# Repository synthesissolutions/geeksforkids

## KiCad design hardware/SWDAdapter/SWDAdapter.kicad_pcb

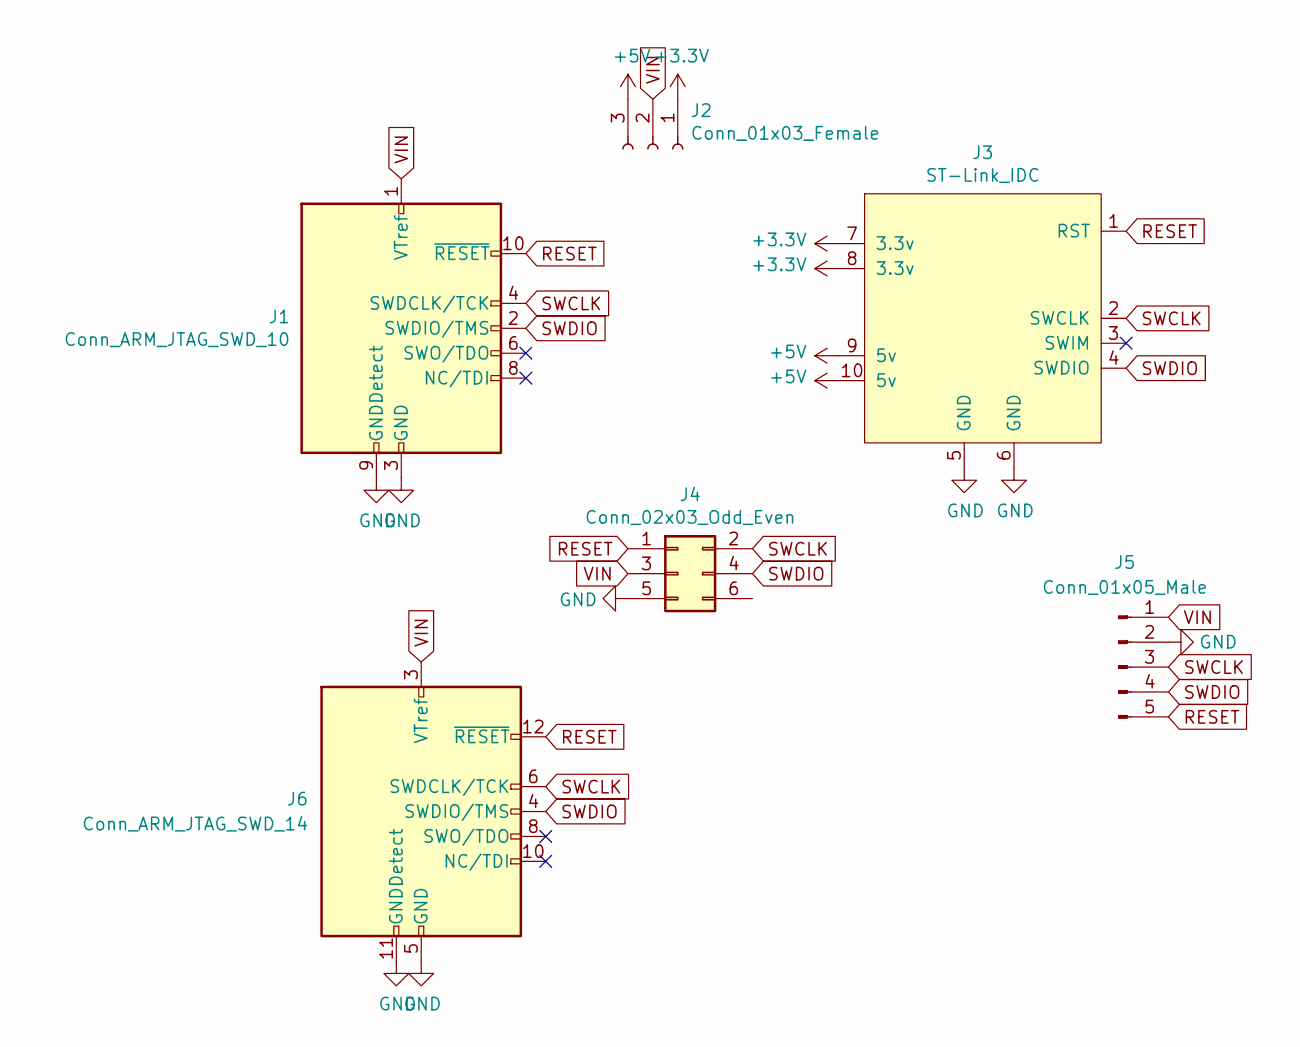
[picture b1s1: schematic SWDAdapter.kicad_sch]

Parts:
J1: Conn_ARM_JTAG_SWD_10; CONN_3220-10-0100-00_CNC
J2: Conn_01x03_Female; PinHeader_1x03_P2.54mm_Vertical
J3: ST-Link_IDC; IDC-Header_2x05_P2.54mm_Vertical
J4: Conn_02x03_Odd_Even; IDC-Header_2x03_P2.54mm_Vertical
J5: Conn_01x05_Male; JST_SH_BM05B-SRSS-TB_1x05-1MP_P1.00mm_Vertical
J6: Conn_ARM_JTAG_SWD_14; SWD14 STLINK-V3-Mini

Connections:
+3V3: J2.1, J3.7 (3.3v), J3.8 (3.3v)
+5V: J2.3, J3.9 (5v), J3.10 (5v)
GND: J1.3 (GND), J1.5 (GND), J1.9 (GNDDetect), J3.5 (GND), J3.6 (GND), J4.5, J5.2, J6.5 (GND), J6.7 (GND), J6.11 (GNDDetect)
RESET: J1.10 (~RESET), J3.1 (RST), J4.1, J5.5, J6.12 (~RESET)
Reserved: J6.1 (Reserved), J6.2 (Reserved), J6.13 (Reserved), J6.14 (Reserved)
SWCLK: J1.4 (SWDCLK/TCK), J3.2 (SWCLK), J4.2, J5.3, J6.6 (SWDCLK/TCK)
SWDIO: J1.2 (SWDIO/TMS), J3.4 (SWDIO), J4.4, J5.4, J6.4 (SWDIO/TMS)
VIN: J1.1 (VTref), J2.2, J4.3, J5.1, J6.3 (VTref)

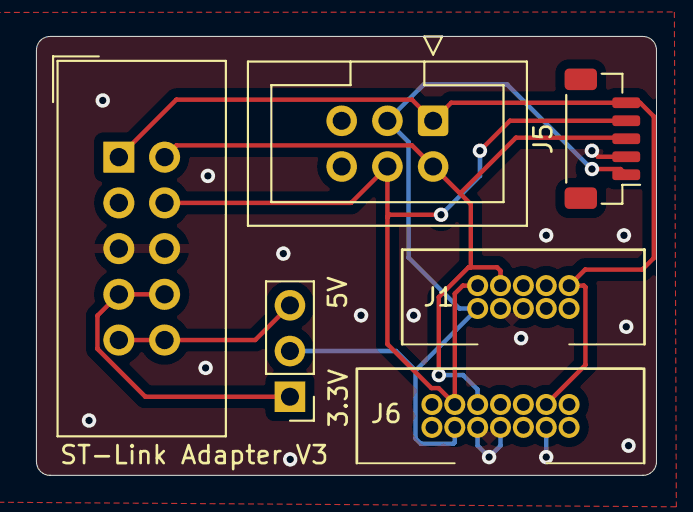
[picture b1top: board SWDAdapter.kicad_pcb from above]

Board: 2 copper layers, 34.4 x 24.4 mm, 6 parts (0 on the bottom side), 8 nets.

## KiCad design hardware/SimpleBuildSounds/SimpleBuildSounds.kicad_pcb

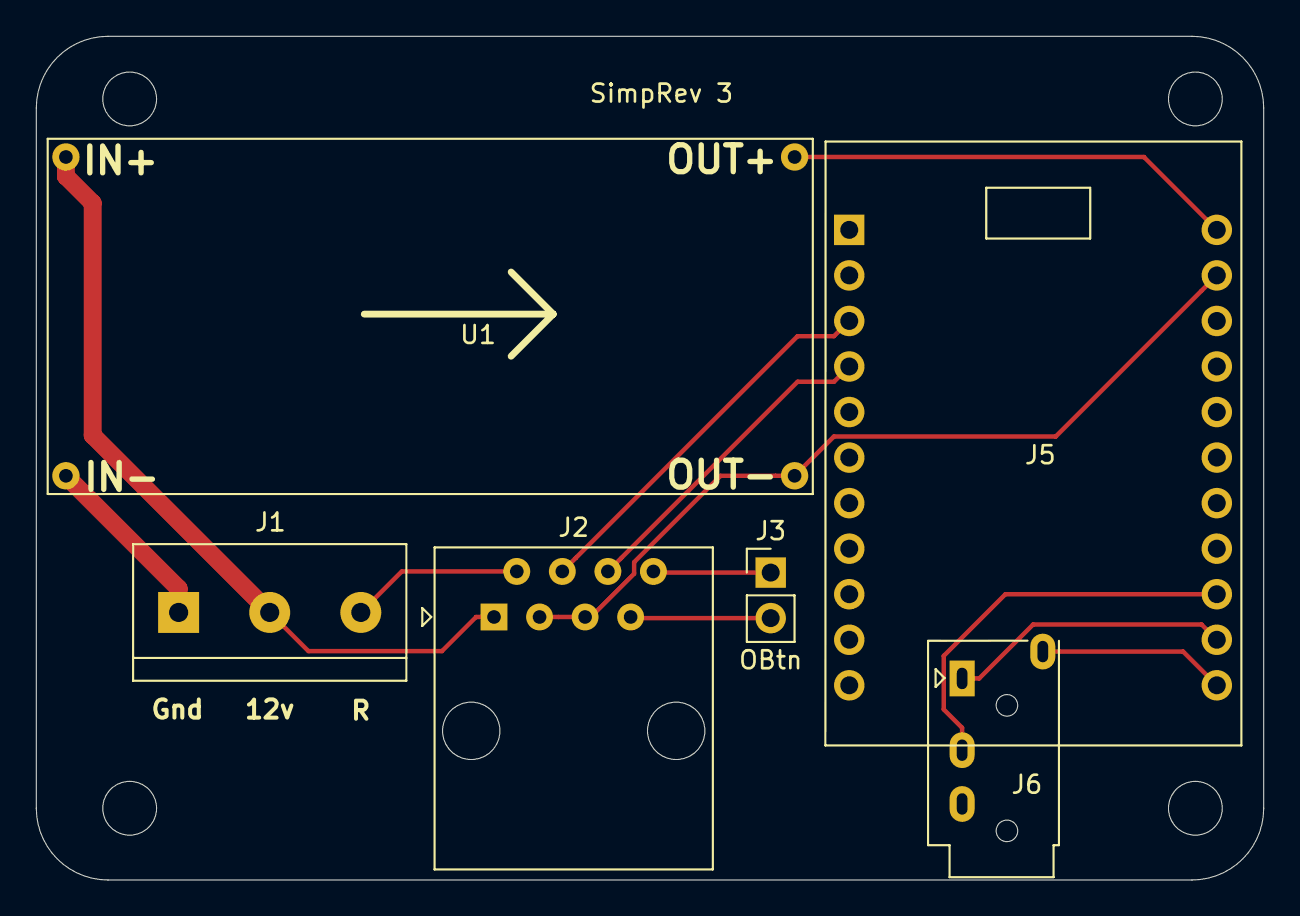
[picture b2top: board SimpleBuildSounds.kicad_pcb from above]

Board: 2 copper layers, 68.5 x 47.1 mm, 10 parts (0 on the bottom side), 12 nets.

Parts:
J1: Power and GoBtn; TerminalBlock_bornier-2_P5.08mm
J2: RJ45; RJ45_Amphenol_54602-x08_Horizontal
J3: OBtn; PinHeader_1x02_P2.54mm_Vertical
J5: FX_Sound; FXSound_2x11_P2.54mm_Short
J6: AudioJack4; Jack_3.5mm_PJ320A_Horizontal
REF: MountingHole_3mm
REF#2, REF#3, REF#4: MountingHole_3mm
U1: LM2596; Regulator_LM2596Adj

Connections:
+5V: J5.2, U1.4
+12V: J1.2, J2.1, U1.2
GND: J2.3, J2.5, J5.4, U1.6
GNDPWR: J1.1, U1.1
unnamed: J1.3, J2.2
unnamed: J2.4, J5.5
unnamed: J2.6, J5.7
unnamed: J2.7, J3.2
unnamed: J2.8, J3.1
unnamed: J5.18, J6.R1
unnamed: J5.20, J6.T
unnamed: J5.22, J6.S

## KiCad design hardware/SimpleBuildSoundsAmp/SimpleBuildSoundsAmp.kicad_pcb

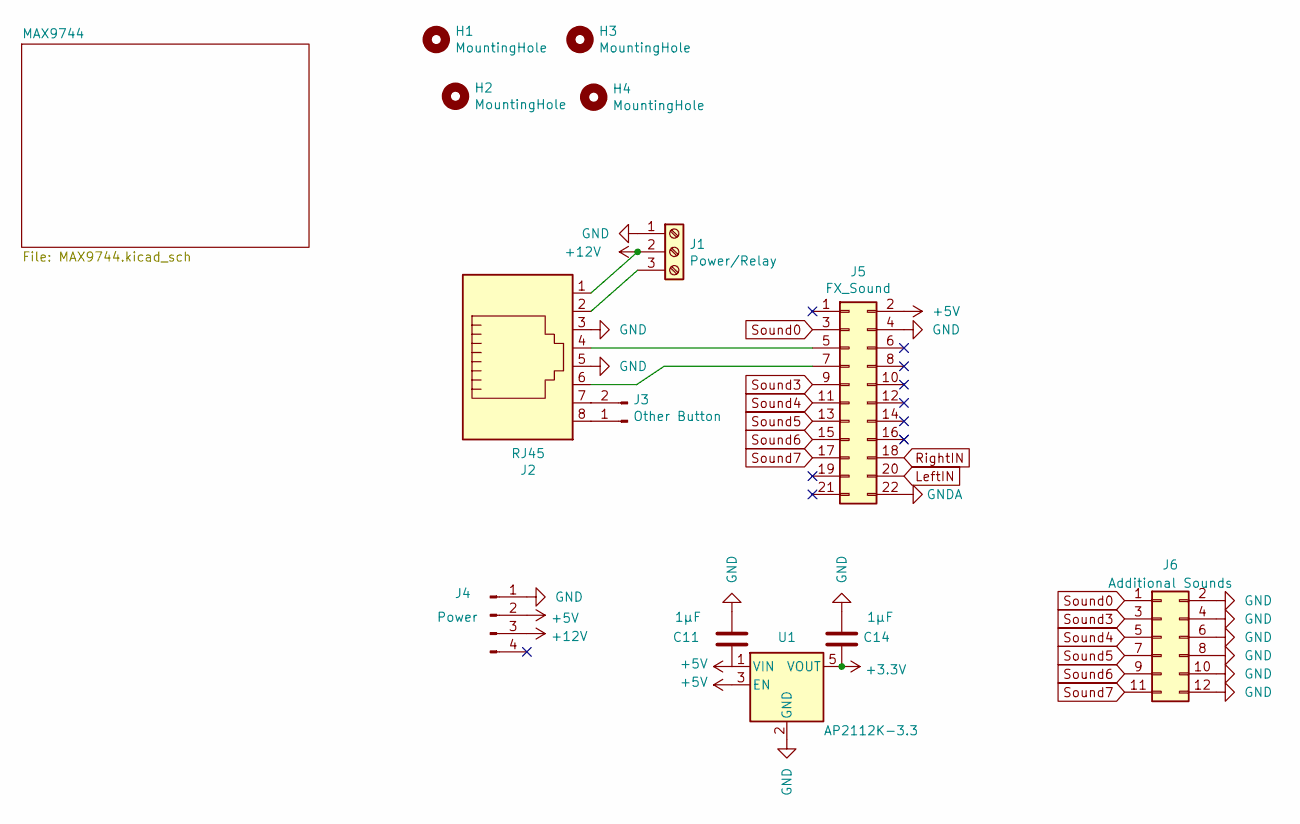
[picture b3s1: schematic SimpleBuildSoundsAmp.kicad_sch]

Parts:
C11, C14: 1µF; C_0805_2012Metric_Pad1.15x1.40mm_HandSolder; DigiKey ID 399-8000-1-ND
H1, H2, H3, H4: MountingHole; MountingHole_2.5mm
J1: Power/Relay; TerminalBlock_bornier-3_P5.08mm
J2: RJ45; RJ45_x08_Tab_Up
J3: Other Button; PinHeader_1x02_P2.54mm_Vertical
J4: Power; AdaFruit_MPM3610
J5: FX_Sound; FXSound_2x11_P2.54mm
J6: Additional Sounds; PinSocket_2x06_P2.54mm_Vertical
U1: AP2112K-3.3; SOT-23-5

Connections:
+3.3V: C14.2, U1.5 (VOUT); also elsewhere on the board
+5V: C11.2, J4.2, J5.2, U1.1 (VIN), U1.3 (EN)
+12V: J1.2, J2.1, J4.3; also elsewhere on the board
GND: C11.1, C14.1, J1.1, J2.3, J2.5, J4.1, J5.4, J6.2, J6.4, J6.6, J6.8, J6.10, J6.12, U1.2 (GND); also elsewhere on the board
GNDA: J5.22; also elsewhere on the board
LeftIN: J5.20; also elsewhere on the board
unnamed: J1.3, J2.2
unnamed: J2.4, J5.5
unnamed: J2.6, J5.7
unnamed: J2.7, J3.2
unnamed: J2.8, J3.1
RightIN: J5.18; also elsewhere on the board
Sound0: J5.3, J6.1
Sound3: J5.9, J6.3
Sound4: J5.11, J6.5
Sound5: J5.13, J6.7
Sound6: J5.15, J6.9
Sound7: J5.17, J6.11

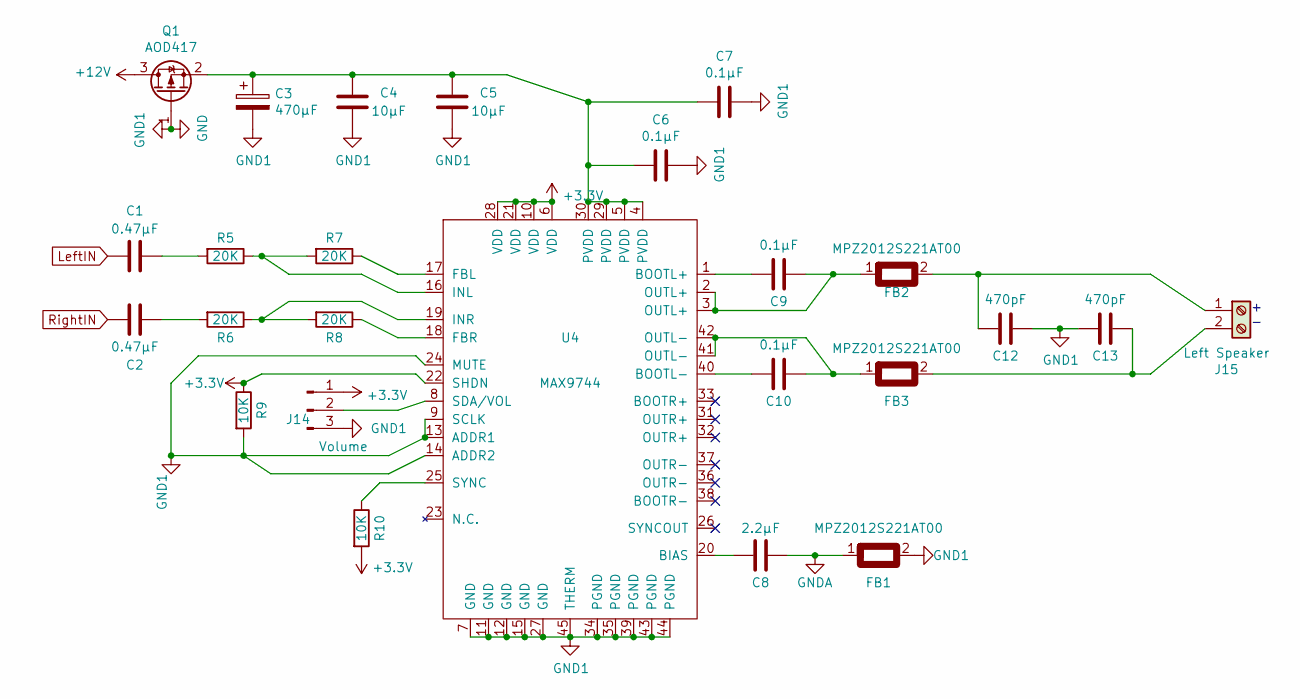
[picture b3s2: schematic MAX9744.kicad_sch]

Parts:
C1, C2: 0.47µF; C_0805_2012Metric_Pad1.15x1.40mm_HandSolder; DigiKey ID 399-8099-1-ND
C3: 470µF; CP_Radial_D8.0mm_P3.50mm; DigiKey ID 1189-1859-ND
C4, C5: 10µF; C_0805_2012Metric_Pad1.15x1.40mm_HandSolder; DigiKey ID 399-8012-1-ND
C6, C7, C9, C10: 0.1µF; C_0805_2012Metric_Pad1.15x1.40mm_HandSolder; DigiKey ID 399-8000-1-ND
C8: 2.2µF; C_0805_2012Metric_Pad1.15x1.40mm_HandSolder; DigiKey ID 399-11941-1-ND
C12, C13: 470pF; C_0805_2012Metric_Pad1.15x1.40mm_HandSolder; DigiKey ID 399-1142-1-ND
FB1, FB2, FB3: MPZ2012S221AT00; L_0805_2012Metric_Pad1.15x1.40mm_HandSolder; DigiKey ID 445-1568-1-ND
J14: Volume; JST_XH_B3B-XH-A_1x03_P2.54mm_Vertical
J15: Left Speaker; TerminalBlock_bornier-2_P5.08mm
Q1: AOD417; TO-252-2pin3D; DigiKey ID 785-1106-1-ND
R5, R6, R7, R8: 20K; R_0805_2012Metric_Pad1.15x1.40mm_HandSolder; DigiKey ID 311-20.0KCRCT-ND
R9, R10: 10K; R_0805_2012Metric_Pad1.15x1.40mm_HandSolder; DigiKey ID RNCP0805FTD10K0CT-ND
U4: MAX9744; max9744eth&plus_Mod; DigiKey ID MAX9744ETH+-ND

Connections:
+3.3V: J14.1, R9.1, R10.2, U4.6 (VDD), U4.10 (VDD), U4.21 (VDD), U4.22 (SHDN), U4.28 (VDD); also elsewhere on the board
+12V: Q1.3 (D); also elsewhere on the board
GND: C3.2, C4.1, C5.1, C6.1, C7.1, C12.1, C13.2, FB1.2, J14.3, Q1.1 (G), R9.2, U4.7 (GND), U4.9 (SCLK), U4.11 (GND), U4.12 (GND), U4.13 (ADDR1), U4.14 (ADDR2), U4.15 (GND), U4.24 (MUTE), U4.27 (GND), U4.34 (PGND), U4.35 (PGND), U4.39 (PGND), U4.43 (PGND), U4.44 (PGND), U4.45 (THERM); also elsewhere on the board
GNDA: C8.2, FB1.1; also elsewhere on the board
LeftIN: C1.2; also elsewhere on the board
unnamed: C1.1, R5.2
unnamed: C2.1, R6.2
unnamed: C3.1, C4.2, C5.2, C6.2, C7.2, Q1.2 (S), U4.4 (PVDD), U4.5 (PVDD), U4.29 (PVDD), U4.30 (PVDD)
unnamed: C8.1, U4.20 (BIAS)
unnamed: C9.1, FB2.1, U4.2 (OUTL+), U4.3 (OUTL+)
unnamed: C9.2, U4.1 (BOOTL+)
unnamed: C10.1, FB3.1, U4.41 (OUTL-), U4.42 (OUTL-)
unnamed: C10.2, U4.40 (BOOTL-)
unnamed: C12.2, FB2.2, J15.1
unnamed: C13.1, FB3.2, J15.2
unnamed: J14.2, U4.8 (SDA/VOL)
unnamed: R5.1, R7.2, U4.16 (INL)
unnamed: R6.1, R8.2, U4.19 (INR)
unnamed: R7.1, U4.17 (FBL)
unnamed: R8.1, U4.18 (FBR)
unnamed: R10.1, U4.25 (SYNC)
RightIN: C2.2; also elsewhere on the board

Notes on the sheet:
+ -

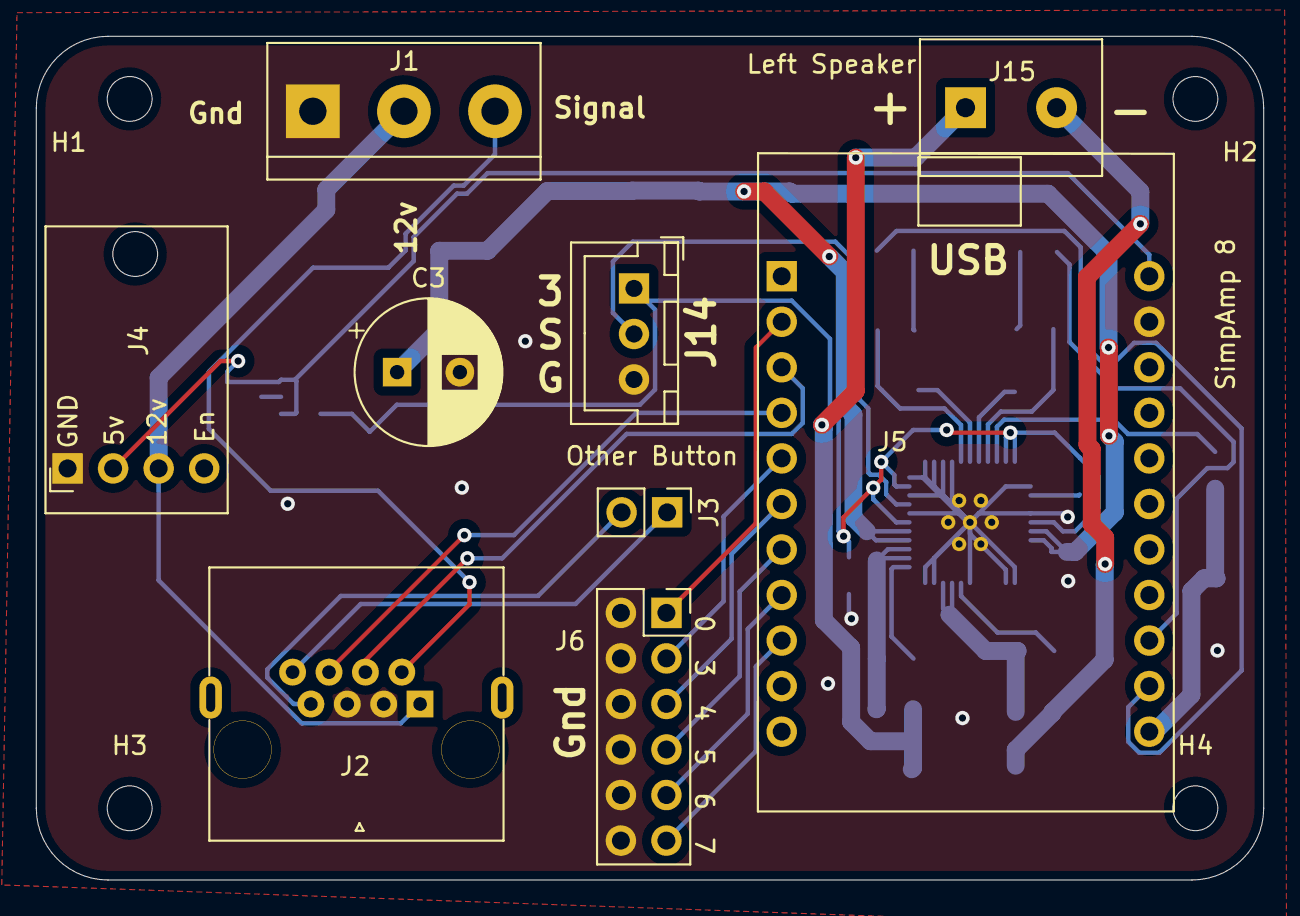
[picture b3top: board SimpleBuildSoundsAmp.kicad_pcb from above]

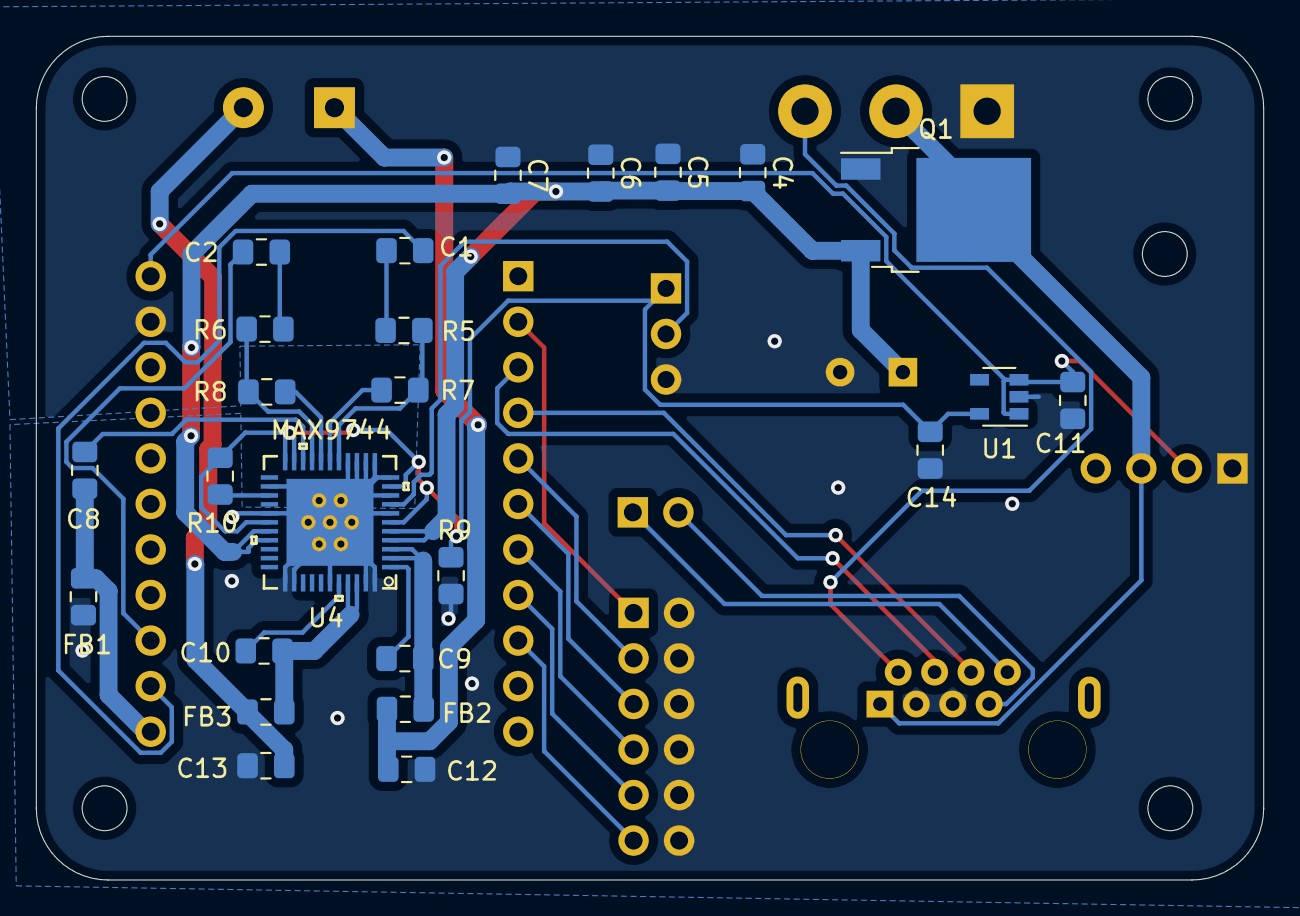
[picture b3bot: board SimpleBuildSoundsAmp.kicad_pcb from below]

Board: 2 copper layers, 68.5 x 47.1 mm, 38 parts (25 on the bottom side), 34 nets.

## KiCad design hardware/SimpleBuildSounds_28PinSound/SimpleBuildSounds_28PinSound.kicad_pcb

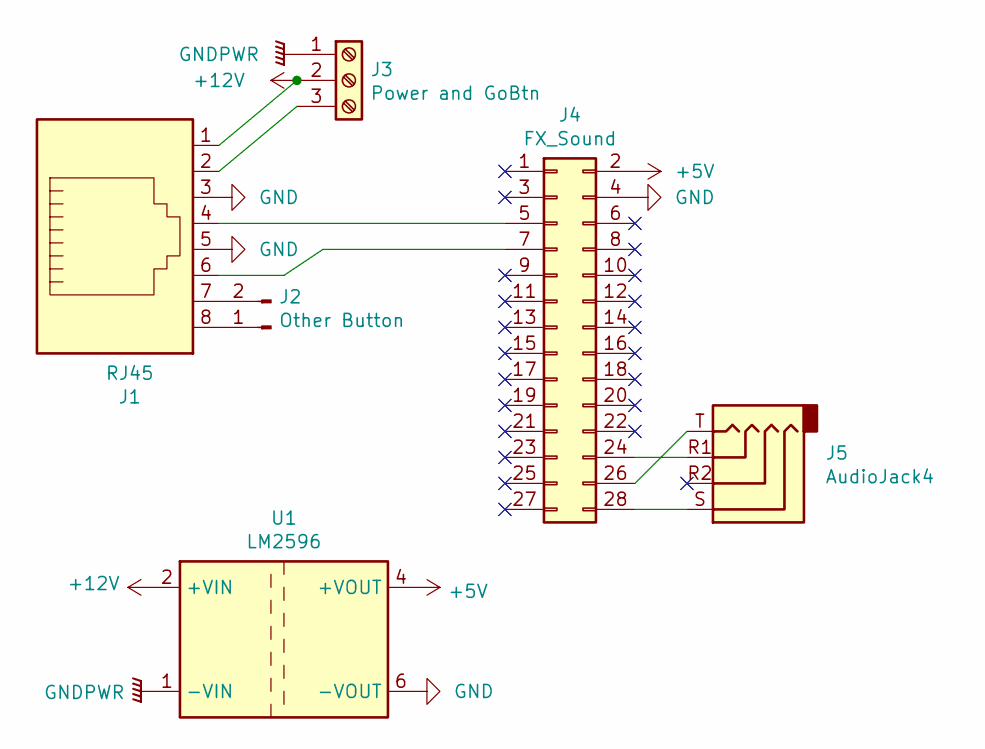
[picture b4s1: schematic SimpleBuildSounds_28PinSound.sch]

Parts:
J1: RJ45; RJ45_Amphenol_54602-x08_Horizontal
J2: Other Button; PinHeader_1x02_P2.54mm_Vertical
J3: Power and GoBtn; TerminalBlock_bornier-3_P5.08mm
J4: FX_Sound; FXSound_HeadPhone_2x14_P2.54mm_Short
J5: AudioJack4; Jack_3.5mm_PJ320A_Horizontal
U1: LM2596; Regulator_LM2596Adj

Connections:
+5V: J4.2, U1.4 (+VOUT)
+12V: J1.1, J3.2, U1.2 (+VIN)
GND: J1.3, J1.5, J4.4, U1.6 (-VOUT)
GNDPWR: J3.1, U1.1 (-VIN)
unnamed: J1.2, J3.3
unnamed: J1.4, J4.5
unnamed: J1.6, J4.7
unnamed: J1.7, J2.2
unnamed: J1.8, J2.1
unnamed: J4.24, J5.R1
unnamed: J4.26, J5.T
unnamed: J4.28, J5.S

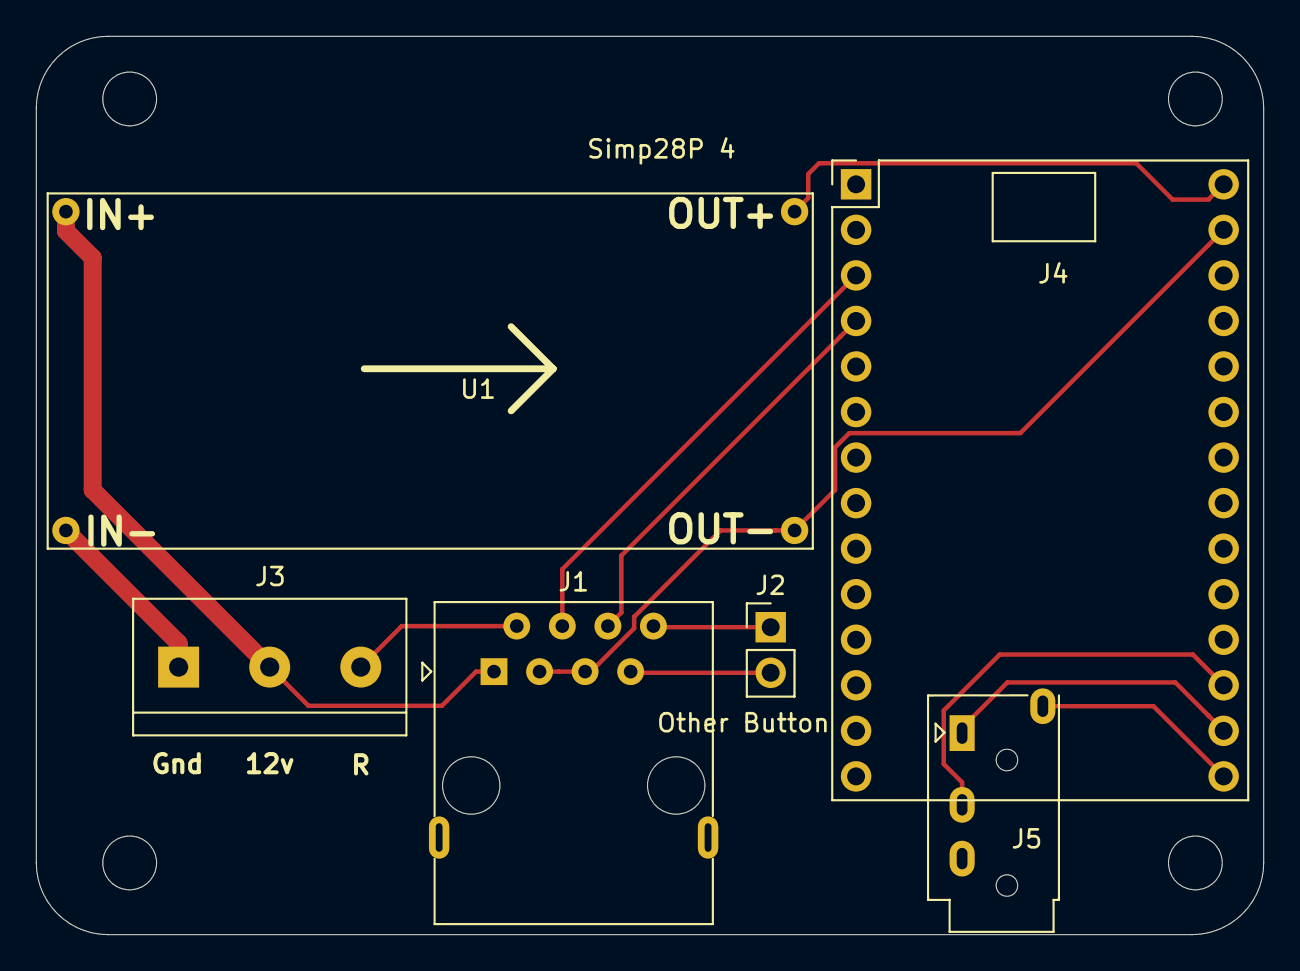
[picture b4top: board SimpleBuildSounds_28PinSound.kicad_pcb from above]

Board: 2 copper layers, 68.5 x 50.1 mm, 10 parts (0 on the bottom side), 12 nets.

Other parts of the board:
REF: MountingHole_3mm
REF#2, REF#3, REF#4: MountingHole_3mm

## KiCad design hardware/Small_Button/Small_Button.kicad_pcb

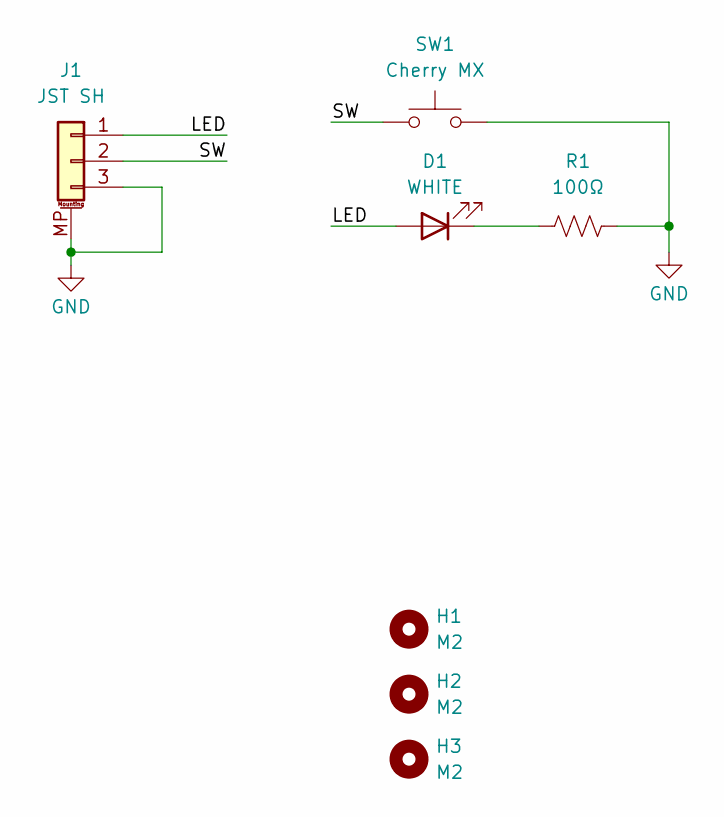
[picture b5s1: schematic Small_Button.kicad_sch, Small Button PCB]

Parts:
D1: WHITE; LED_D3.0mm; MPN C210322
H1, H2, H3: M2; MountingHole_2.2mm_M2_DIN965
J1: JST SH; JST_SH_SM03B-SRSS-TB_1x03-1MP_P1.00mm_Horizontal; MPN C160403
R1: 100Ω; R_0603_1608Metric; MPN C22775
SW1: Cherry MX; SW_Cherry_MX_1.00u_PCB; MPN C400229

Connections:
/LED: D1.2 (A), J1.1
/SW: J1.2, SW1.1
GND: J1.3, J1.MP (MountPin), R1.2, SW1.2
unnamed: D1.1 (K), R1.1

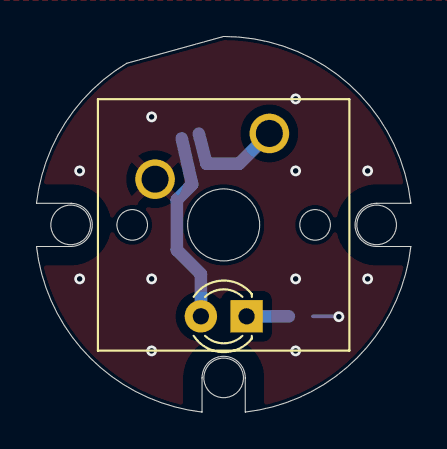
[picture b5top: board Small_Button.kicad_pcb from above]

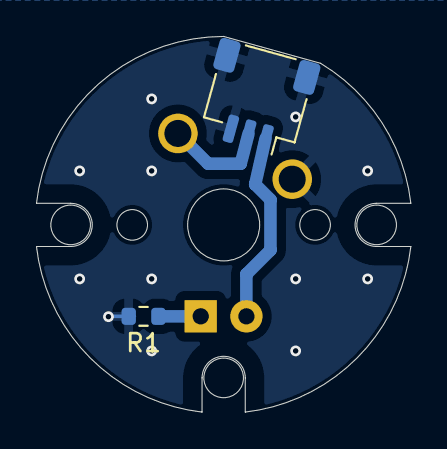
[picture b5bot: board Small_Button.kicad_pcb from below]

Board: 2 copper layers, 20.8 x 20.9 mm, 7 parts (2 on the bottom side), 4 nets.

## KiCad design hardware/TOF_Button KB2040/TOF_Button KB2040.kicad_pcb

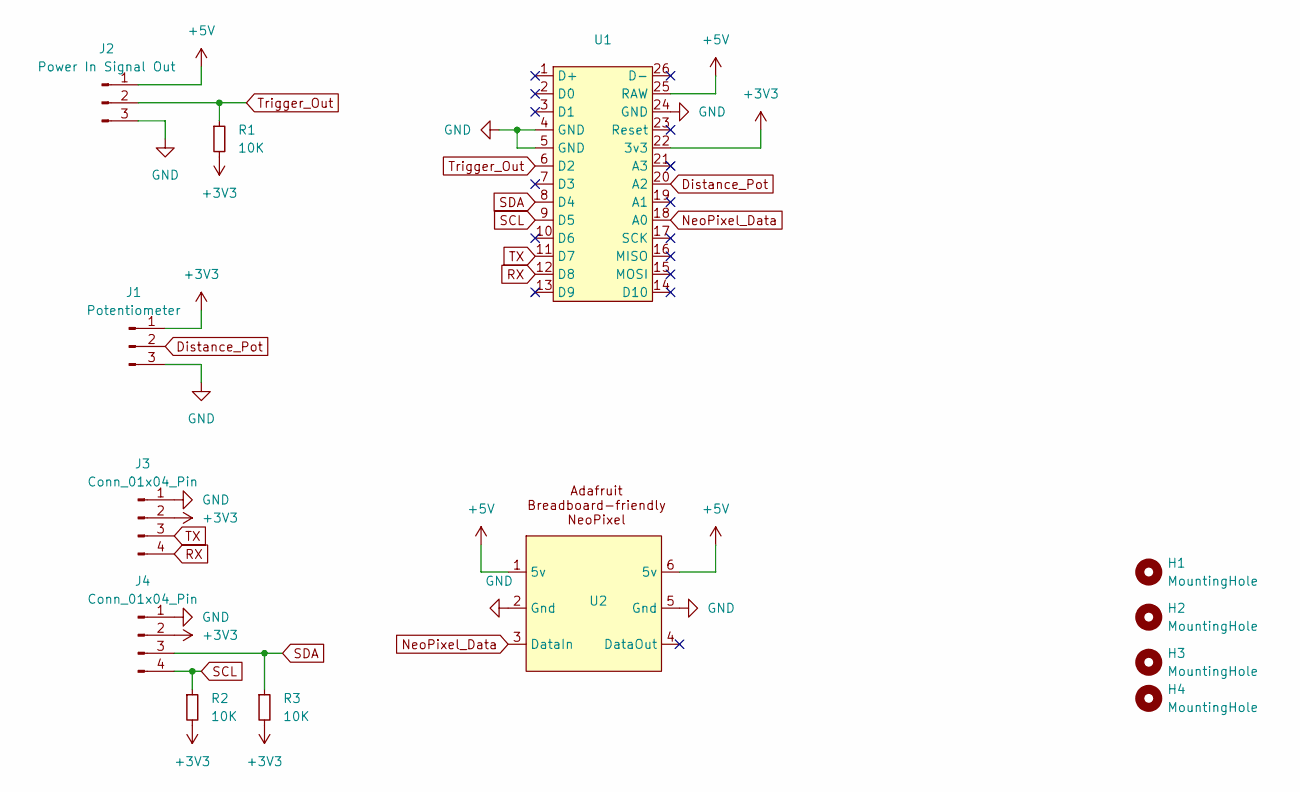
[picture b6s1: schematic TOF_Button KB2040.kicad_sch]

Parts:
H1, H2, H3, H4: MountingHole; MountingHole_3.2mm_M3
J1: Potentiometer; JST_XH_B3B-XH-A_1x03_P2.50mm_Vertical
J2: Power In Signal Out; JST_XH_B3B-XH-A_1x03_P2.50mm_Vertical
J3, J4: Conn_01x04_Pin; JST_XH_B4B-XH-A_1x04_P2.50mm_Vertical
R1, R2, R3: 10K; R_Axial_DIN0204_L3.6mm_D1.6mm_P7.62mm_Horizontal
U1: Adafruit KB2040
U2: NeoPixel_Breadboard

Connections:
+3V3: J1.1, J3.2, J4.2, R1.2, R2.2, R3.2, U1.22 (3v3)
+5V: J2.1, U1.25 (RAW), U2.1 (5v), U2.6 (5v)
Distance_Pot: J1.2, U1.20 (A2)
GND: J1.3, J2.3, J3.1, J4.1, U1.4 (GND), U1.5 (GND), U1.24 (GND), U2.2 (Gnd), U2.5 (Gnd)
NeoPixel_Data: U1.18 (A0), U2.3 (DataIn)
RX: J3.4, U1.12 (D8)
SCL: J4.4, R2.1, U1.9 (D5)
SDA: J4.3, R3.1, U1.8 (D4)
TX: J3.3, U1.11 (D7)
Trigger_Out: J2.2, R1.1, U1.6 (D2)

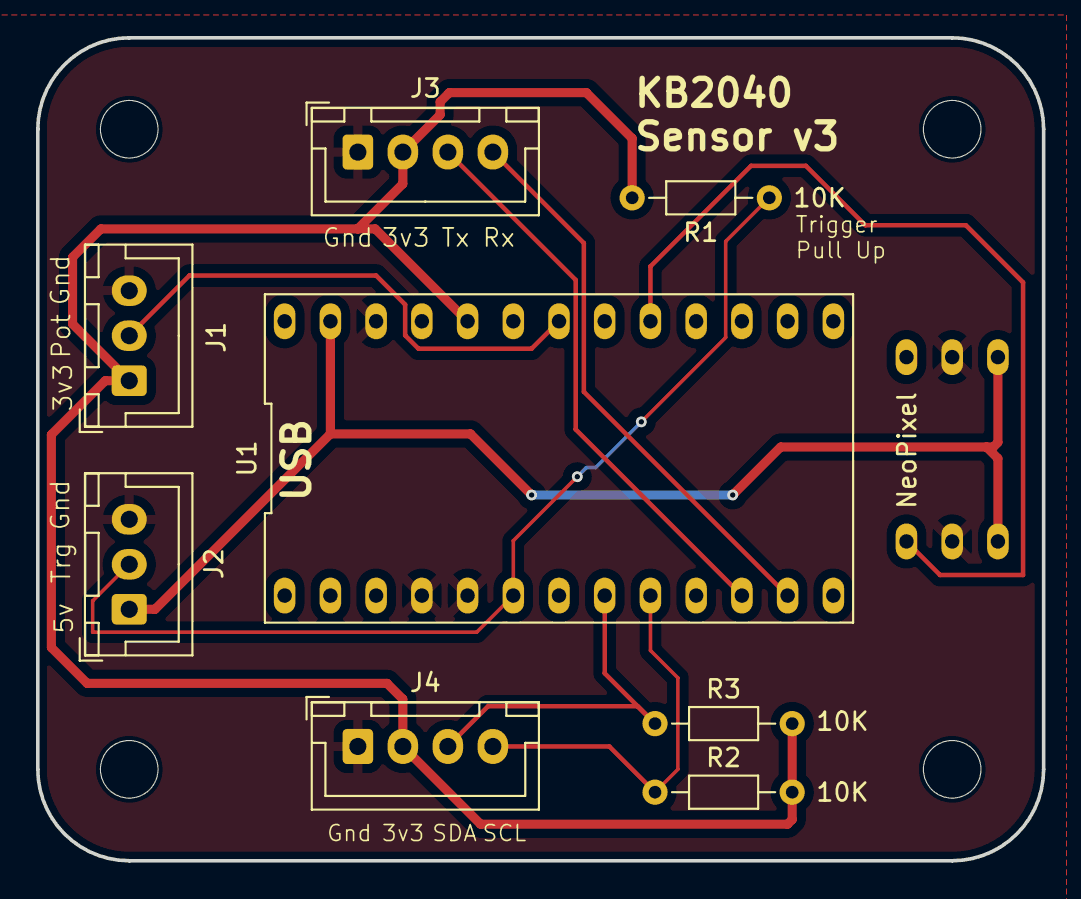
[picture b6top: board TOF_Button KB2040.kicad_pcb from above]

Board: 2 copper layers, 55.9 x 45.7 mm, 13 parts (1 on the bottom side), 10 nets.
